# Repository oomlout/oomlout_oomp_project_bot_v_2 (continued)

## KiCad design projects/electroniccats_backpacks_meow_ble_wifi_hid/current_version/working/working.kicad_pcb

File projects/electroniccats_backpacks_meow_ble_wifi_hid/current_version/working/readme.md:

# backpacks_meow
 
## summary 
* id: electroniccats_backpacks_meow_ble_wifi_hid
* user: electroniccats
* name: backpacks_meow
* board: ble_wifi_hid
* repo: https://github.com/ElectronicCats/Backpacks_Meow
* src_file_repo_kicad_pcb: BLE_WIFI_HID/BLE_WIFI_HID.kicad_pcb
* src_file_repo_kicad_pcb_link: https://github.com/ElectronicCats/Backpacks_Meow/tree/master/BLE_WIFI_HID/BLE_WIFI_HID.kicad_pcb

* src_file_repo_sch: BLE_WIFI_HID/BLE_WIFI_HID.sch
* src_file_repo_sch_link: https://github.com/ElectronicCats/Backpacks_Meow/tree/master/BLE_WIFI_HID/BLE_WIFI_HID.sch
* full details link: https://github.com/oomlout/oomlout_oomp_project_bot_v_2/tree/main/projects/electroniccats_backpacks_meow_ble_wifi_hid/current_version/working

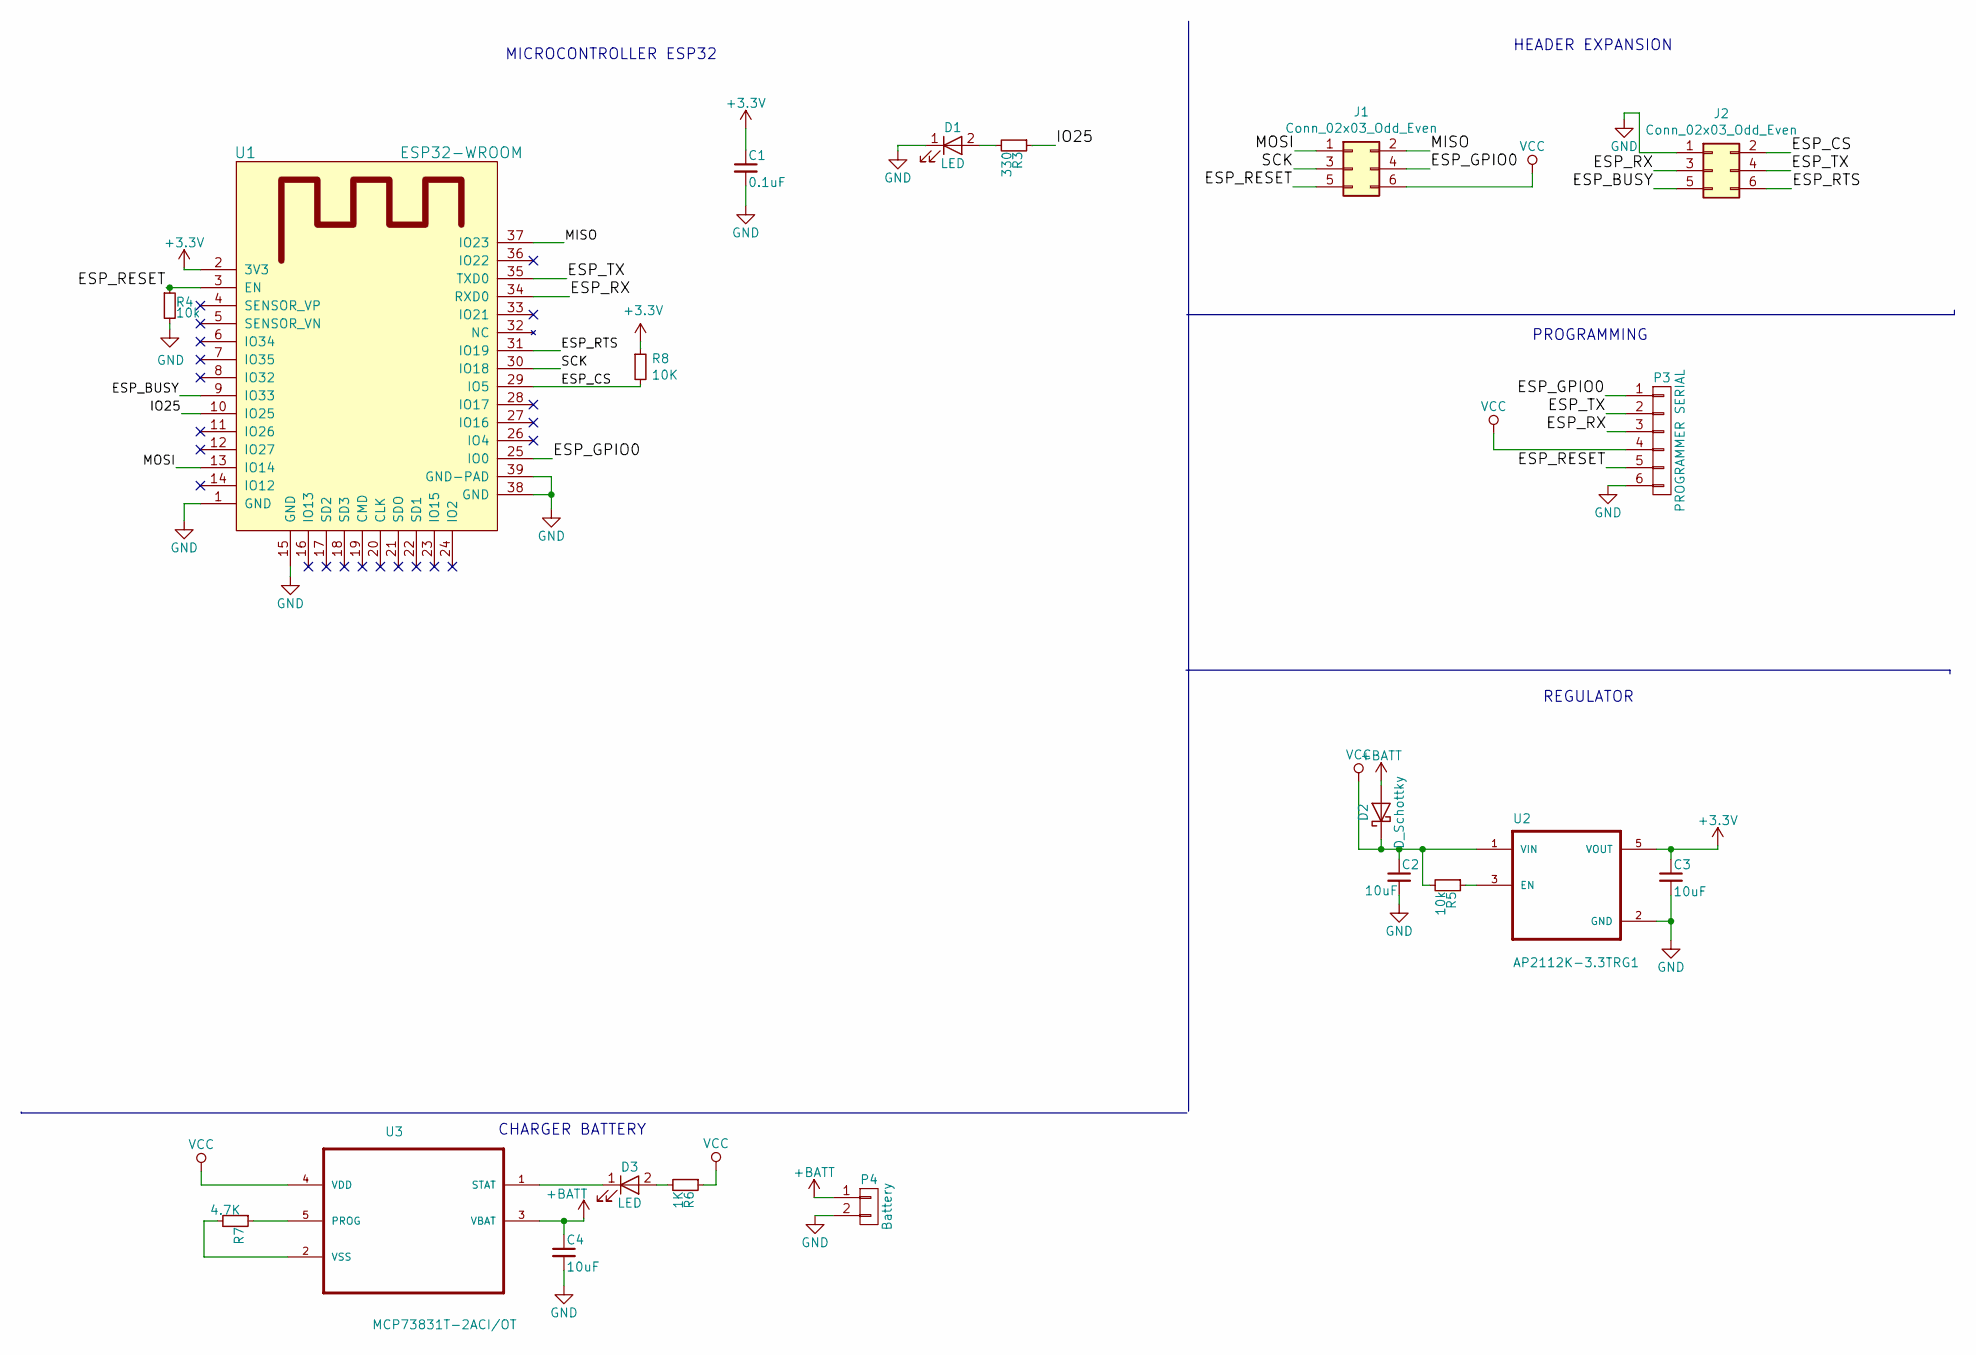
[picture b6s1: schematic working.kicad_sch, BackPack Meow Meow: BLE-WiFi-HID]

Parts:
C1: 0.1uF; C_0805_HandSoldering
C2, C3, C4: 10uF; C_0805_HandSoldering
D1, D3: LED; LED_0805_HandSoldering
D2: D_Schottky; D_SOD-123F
J1, J2: Conn_02x03_Odd_Even; 62000621121
P3: PROGRAMMER SERIAL; Pin_Header_Straight_1x06_Pitch2.54mm
P4: Battery; Pin_Header_Straight_1x02_Pitch2.54mm
R3: 330; R_0805_HandSoldering
R4, R5: 10k; R_0805_HandSoldering
R6: 1K; R_0805_HandSoldering
R7: 4.7K; R_0805_HandSoldering
R8: 10K; R_0805_HandSoldering
U1: ESP32-WROOM
U2: AP2112K-3.3TRG1; SOT-23-5_HandSoldering
U3: MCP73831T-2ACI/OT; SOT-23-5_HandSoldering

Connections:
+3V3: C1.1, C3.1, R8.1, U1.2 (3V3), U2.5 (VOUT)
+BATT: C4.1, D2.2 (A), P4.1, U3.3 (VBAT); also elsewhere on the board
/ESP_BUSY: J2.5, U1.9 (IO33)
/ESP_CS: J2.2, R8.2, U1.29 (IO5)
/ESP_GPIO0: J1.4, P3.1, U1.25 (IO0)
/ESP_RESET: J1.5, P3.5, R4.1, U1.3 (EN)
/ESP_RTS: J2.6, U1.31 (IO19)
/ESP_RX: J2.3, P3.3, U1.34 (RXD0)
/ESP_TX: J2.4, P3.2, U1.35 (TXD0)
/IO25: R3.1, U1.10 (IO25)
/MISO: J1.2, U1.37 (IO23)
/MOSI: J1.1, U1.13 (IO14)
/SCK: J1.3, U1.30 (IO18)
GND: C1.2, C2.2, C3.2, C4.2, D1.1 (K), J2.1, P3.6, P4.2, R4.2, U1.1 (GND), U1.15 (GND), U1.38 (GND), U1.39 (GND-PAD), U2.2 (GND); also elsewhere on the board
unnamed: D1.2 (A), R3.2
unnamed: D3.1 (K), U3.1 (STAT)
unnamed: D3.2 (A), R6.2
unnamed: R5.1, U2.3 (EN)
unnamed: R7.1, U3.5 (PROG)
unnamed: R7.2, U3.2 (VSS)
VCC: C2.1, D2.1 (K), J1.6, P3.4, R5.2, R6.1, U2.1 (VIN), U3.4 (VDD)

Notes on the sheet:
HEADER EXPANSION
MICROCONTROLLER ESP32
CHARGER BATTERY
PROGRAMMING
REGULATOR

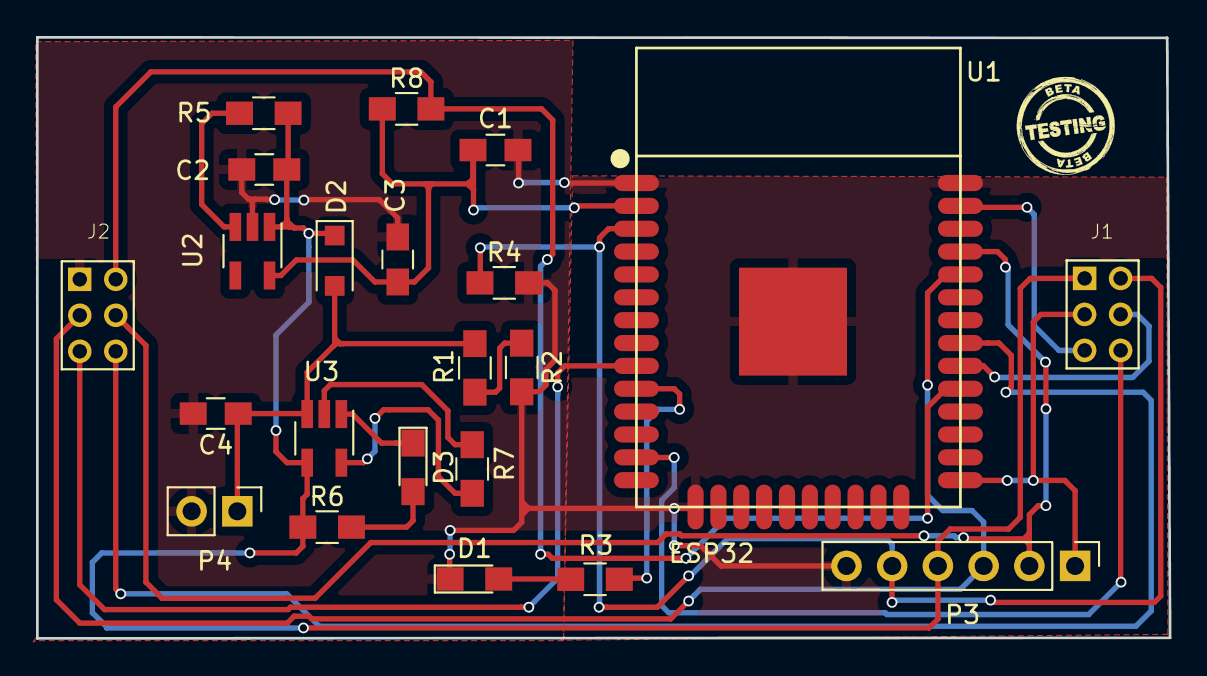
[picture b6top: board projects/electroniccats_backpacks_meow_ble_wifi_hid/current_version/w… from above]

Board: 2 copper layers, 62.9 x 33.4 mm, 22 parts (0 on the bottom side), 22 nets.

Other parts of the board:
R1, R2: 100k; R_0805_HandSoldering

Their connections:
+BATT: R1.1; also elsewhere on the board
/AN35_BAT: R1.2, R2.1
GND: R2.2; also elsewhere on the board

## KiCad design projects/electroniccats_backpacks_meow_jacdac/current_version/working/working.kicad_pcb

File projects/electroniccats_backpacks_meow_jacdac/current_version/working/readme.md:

# backpacks_meow
 
## summary 
* id: electroniccats_backpacks_meow_jacdac
* user: electroniccats
* name: backpacks_meow
* board: jacdac
* repo: https://github.com/ElectronicCats/Backpacks_Meow
* src_file_repo_kicad_pcb: jacdac/jacdac.kicad_pcb
* src_file_repo_kicad_pcb_link: https://github.com/ElectronicCats/Backpacks_Meow/tree/master/jacdac/jacdac.kicad_pcb

* src_file_repo_sch: jacdac/jacdac.sch
* src_file_repo_sch_link: https://github.com/ElectronicCats/Backpacks_Meow/tree/master/jacdac/jacdac.sch
* full details link: https://github.com/oomlout/oomlout_oomp_project_bot_v_2/tree/main/projects/electroniccats_backpacks_meow_jacdac/current_version/working

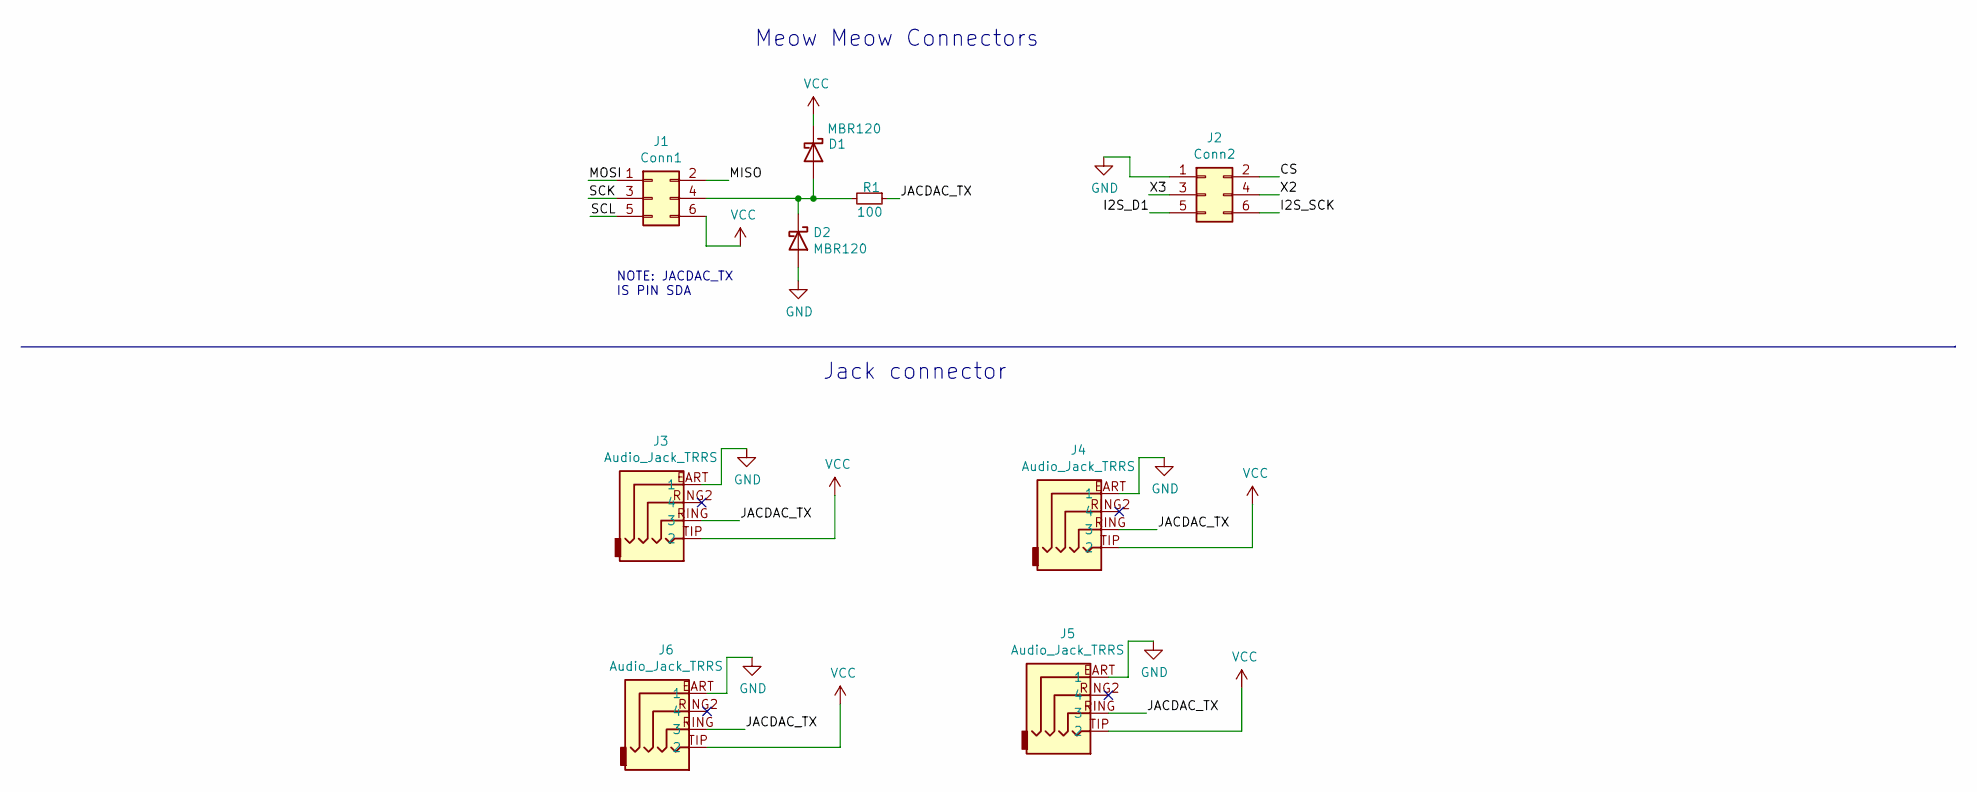
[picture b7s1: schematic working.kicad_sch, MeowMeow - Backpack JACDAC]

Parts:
D1, D2: MBR120; D_SOD-123F
J1: Conn1; 61300621121
J2: Conn2; 61300621121
J3, J4, J5, J6: Audio_Jack_TRRS; AUDIO-JACK-TRRS-SMD
R1: 100; R_0805_HandSoldering

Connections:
/CS: J2.2
/I2S_D1: J2.5
/I2S_SCK: J2.6
/JACDAC_TX: J3.RING (3), J4.RING (3), J5.RING (3), J6.RING (3), R1.1
/MISO: J1.2
/MOSI: J1.1
/SCK: J1.3
/SCL: J1.5
/X2: J2.4
/X3: J2.3
GND: D2.2 (A), J2.1, J3.EART (1), J4.EART (1), J5.EART (1), J6.EART (1)
unnamed: D1.2 (A), D2.1 (K), J1.4, R1.2
VCC: D1.1 (K), J1.6, J3.TIP (2), J4.TIP (2), J5.TIP (2), J6.TIP (2)

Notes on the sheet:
Meow Meow Connectors
NOTE: JACDAC_TX IS PIN SDA
Jack connector

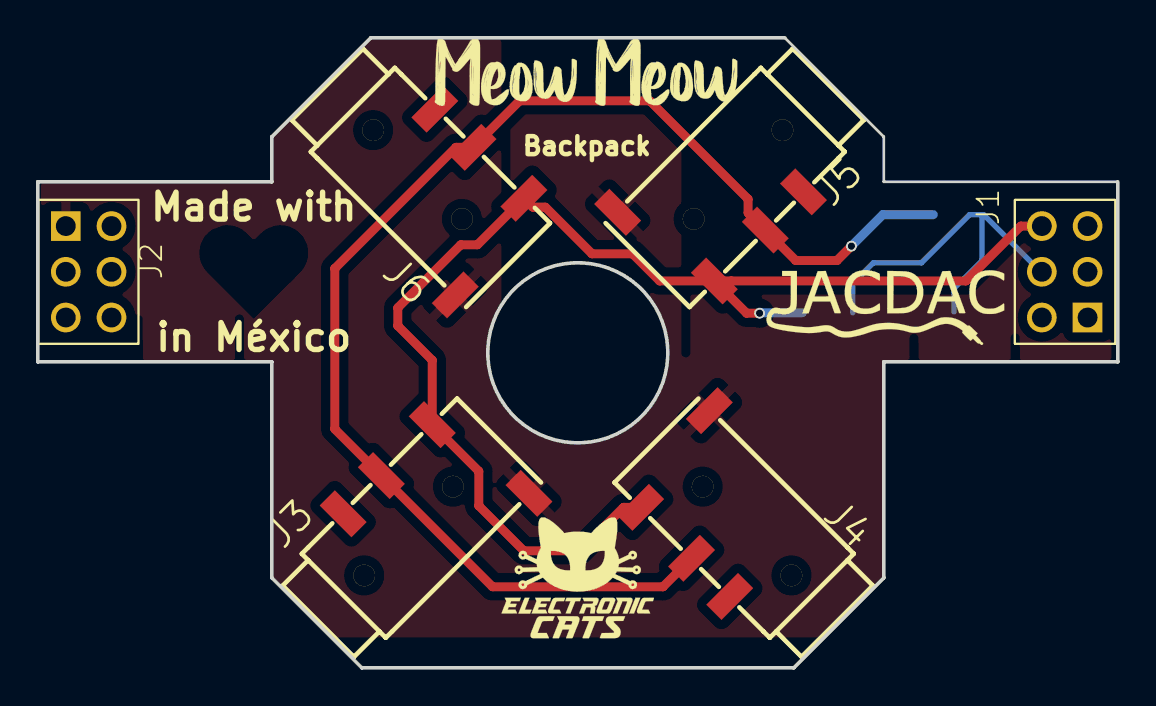
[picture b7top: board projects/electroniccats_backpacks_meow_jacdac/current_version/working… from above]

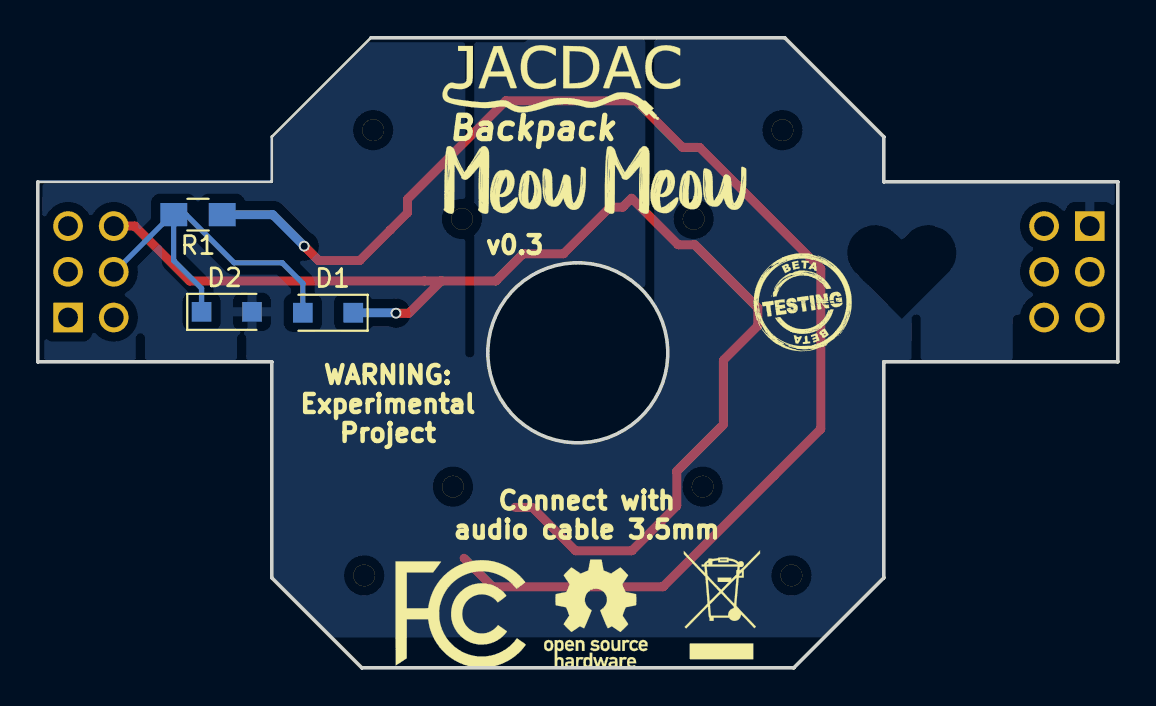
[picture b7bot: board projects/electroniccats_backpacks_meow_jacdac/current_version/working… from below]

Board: 2 copper layers, 60.0 x 35.0 mm, 11 parts (4 on the bottom side), 4 nets.

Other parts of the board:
svg2mod, svg2mod#2: G***; heart_trans

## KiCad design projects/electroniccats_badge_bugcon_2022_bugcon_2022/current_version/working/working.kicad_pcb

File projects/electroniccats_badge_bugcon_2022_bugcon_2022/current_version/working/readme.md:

# badge_bugcon_2022
 
## summary 
* id: electroniccats_badge_bugcon_2022_bugcon_2022
* user: electroniccats
* name: badge_bugcon_2022
* board: bugcon_2022
* repo: https://github.com/ElectronicCats/Badge-BugCON-2022
* src_file_repo_kicad_pcb: Hardware/BugCON-2022.kicad_pcb
* src_file_repo_kicad_pcb_link: https://github.com/ElectronicCats/Badge-BugCON-2022/tree/main/Hardware/BugCON-2022.kicad_pcb
* src_file_repo_kicad_sch: Hardware/BugCON-2022.kicad_sch
* src_file_repo_kicad_sch_link: https://github.com/ElectronicCats/Badge-BugCON-2022/tree/main/Hardware/BugCON-2022.kicad_sch

* src_file_repo_sch: 
* src_file_repo_sch_link: https://github.com/ElectronicCats/Badge-BugCON-2022/tree/main/
* full details link: https://github.com/oomlout/oomlout_oomp_project_bot_v_2/tree/main/projects/electroniccats_badge_bugcon_2022_bugcon_2022/current_version/working

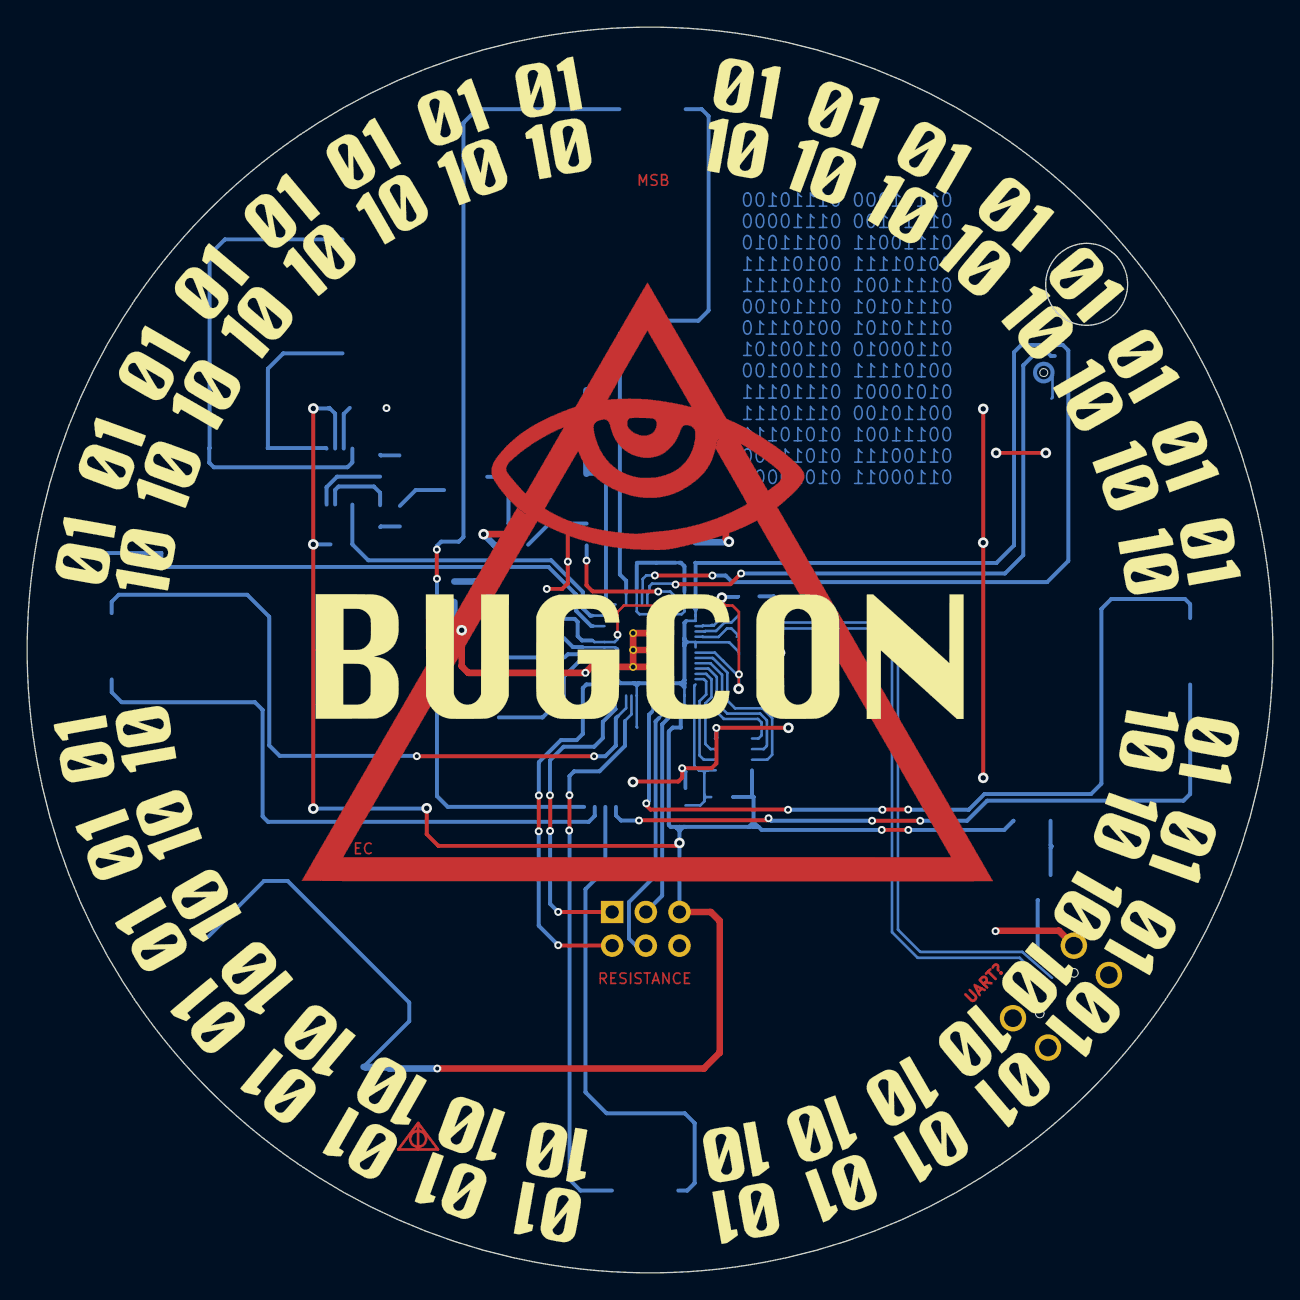
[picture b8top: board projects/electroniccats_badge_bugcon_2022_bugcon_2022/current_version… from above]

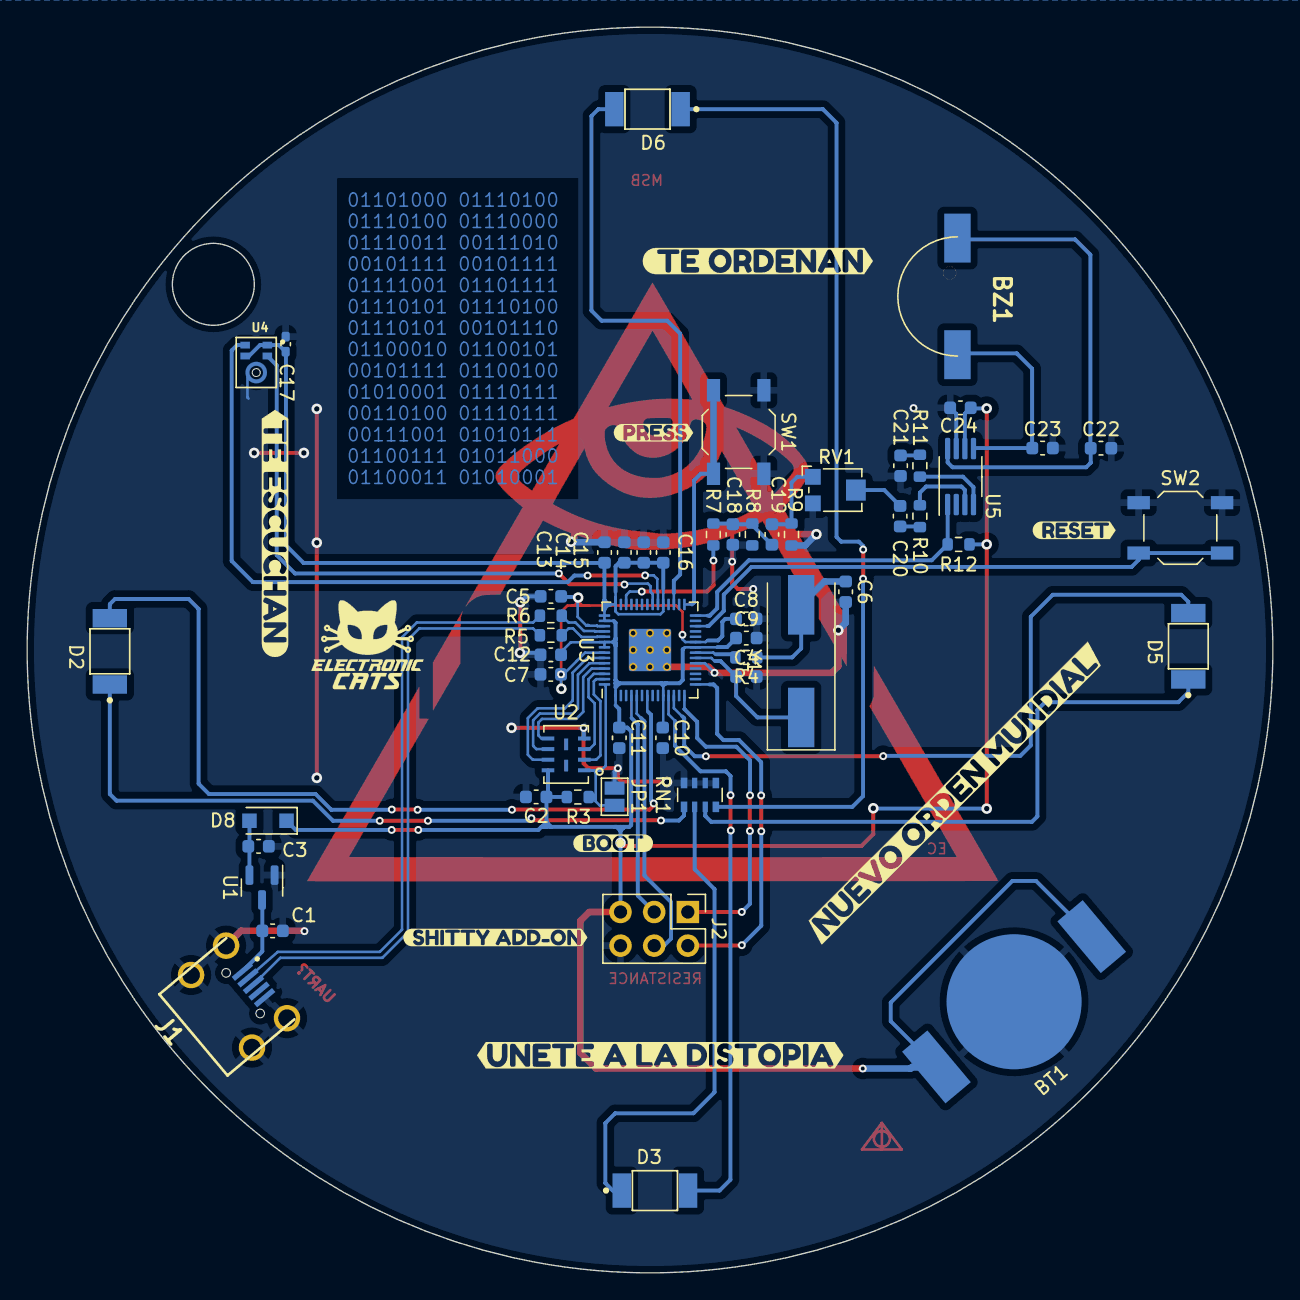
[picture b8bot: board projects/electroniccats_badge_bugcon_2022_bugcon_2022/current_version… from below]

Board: 2 copper layers, 94.0 x 94.0 mm, 63 parts (62 on the bottom side), 45 nets.

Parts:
BT1: Battery_Cell; BAT-HLD-012-SMT-OTL
BZ1: Buzzer; CAPAE1050X250N
C1, C3, C24: 10uF; C_0603_1608Metric
C2, C7, C8, C10, C11, C12, C13, C14, C15, C16: 0.1uF; C_0603_1608Metric
C4, C6: 27pF; C_0603_1608Metric
C5, C9, C20, C21: 1uF; C_0603_1608Metric
C17: 0.1uF; C_0402_1005Metric_Pad0.74x0.62mm_HandSolder
C18: 100nF; C_0603_1608Metric
C19: 47uF; C_0603_1608Metric
C22, C23: 220pF; C_0603_1608Metric
D2, D3, D5, D6: R_LED; LYT77K-K2M1-NoHole
D8: SS1020FL; D_SOD-123F
J1: USB_B_Micro; U254051N4BH806
J2: Conn_02x03_Odd_Even; PinHeader_2x03_P2.54mm_Vertical
JP1: BOOT; SolderJumper-2_P1.3mm_Open_Pad1.0x1.5mm
R3, R12: 10K; R_0603_1608Metric
R4: 1K; R_0603_1608Metric
R5, R6: 27; R_0603_1608Metric
R7: 220; R_0603_1608Metric
R8, R10, R11: 100; R_0603_1608Metric
R9: 1.8K; R_0603_1608Metric
RN1: R_Pack04; R_Array_Convex_4x0603
RV1: 10K; Potentiometer_Bourns_TC33X_Vertical
Ref**: Val**; pin_final_cc
SW1: Button; SW_SPST_TL3342
SW2: RESET; SW_SPST_TL3342
U1: MCP1700-31; SOT-23
U2: W25Q16JV; W25Q16JVUUIQ
U3: RP2040; RP2040-QFN-56
U4: SPH0641LM4H; MIC_SPH0641LM4H-1
U5: PAM8302AAD; MSOP-8_3x3mm_P0.65mm
Y1: 12Mhz; Crystal_SMD_HC49-SD
kibuzzard-6340AD5F: G***; kibuzzard-6340AD5F
kibuzzard-63409D39: G***; kibuzzard-63409D39
kibuzzard-63409DA5: G***; kibuzzard-63409DA5
kibuzzard-63409DC5: G***; kibuzzard-63409DC5
kibuzzard-63409E53: G***; kibuzzard-63409E53
kibuzzard-63409EAE: G***; kibuzzard-63409EAE
kibuzzard-63409EDC: G***; kibuzzard-63409EDC
kibuzzard-63409F0B: G***; kibuzzard-63409F0B

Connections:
+1V2: C5.1, C7.1, C8.1, U3.23 (DVDD), U3.45 (VREG_VOUT), U3.50 (DVDD)
+3V3: BT1.2 (-), C2.1, C9.1, C10.1, C11.1, C12.1, C13.1, C14.1, C15.1, C16.1, C17.1, C24.1, D8.1 (K), J2.5, R3.1, R12.2, U2.8 (VCC), U3.1 (IOVDD), U3.10 (IOVDD), U3.22 (IOVDD), U3.33 (IOVDD), U3.42 (IOVDD), U3.43 (ADC_AVDD), U3.44 (VREG_IN), U3.48 (USB_VDD), U3.49 (IOVDD), U4.1 (VDD), U4.2 (LR), U5.6 (VDD)
/A2: R7.2, U3.40 (GPIO28_ADC2)
/CLK: U3.35 (GPIO23), U4.3 (CLK)
/D0: D2.2 (A), U3.7 (GPIO5)
/D5: D3.2 (A), U3.11 (GPIO8)
/D6: D5.2 (A), U3.12 (GPIO9)
/D10: J2.1, U3.14 (GPIO11)
/D11: J2.2, U3.15 (GPIO12)
/D12: D6.2 (A), U3.31 (GPIO20)
/D+: J1.3 (D+), R5.1
/D-: J1.2 (D-), R6.1
/DOUT: U3.34 (GPIO22), U4.4 (DOUT)
/GPIO17: R12.1, U3.28 (GPIO17), U5.1 (~SD)
/GPIO18: SW1.2, U3.29 (GPIO18)
/QSPI_CS: JP1.2 (B), R3.2, U2.1 (~CS), U3.56 (QSPI_SS)
/QSPI_DATA0: U2.5 (DI(IO0)), U3.53 (QSPI_SD0)
/QSPI_DATA1: U2.2 (DO(IO1)), U3.55 (QSPI_SD1)
/QSPI_DATA2: U2.3 (IO2), U3.54 (QSPI_SD2)
/QSPI_DATA3: U2.7 (IO3), U3.51 (QSPI_SD3)
/QSPI_SCK: U2.6 (CLK), U3.52 (QSPI_SCLK)
/RD+: R5.2, U3.47 (USB_DP)
/RD-: R6.2, U3.46 (USB_DM)
/RST: SW2.2, U3.26 (RUN)
/SCL: J2.4, U3.5 (GPIO3)
/SDA: J2.3, U3.4 (GPIO2)
GND: BT1.1 (+), C1.2, C2.2, C3.2, C4.2, C5.2, C6.2, C7.2, C8.2, C9.2, C10.2, C11.2, C12.2, C13.2, C14.2, C15.2, C16.2, C17.2, C18.2, C21.2, C22.2, C23.2, C24.2, J1.5 (GND), J1.6 (Shield), J2.6, JP1.1 (A), R8.2, R9.2, RN1.5 (R4.2), RN1.6 (R3.2), RN1.7 (R2.2), RN1.8 (R1.2), RV1.3, SW1.1, SW2.1, U1.1 (GND), U2.4 (GND), U3.19 (TESTEN), U3.57 (GND), U4.5 (GND), U5.7 (GND)
unnamed: BZ1.1 (-), C23.1, U5.5 (OUT+)
unnamed: BZ1.2 (+), C22.1, U5.8 (OUT-)
unnamed: C3.1, D8.2 (A), U1.2 (VO)
unnamed: C4.1, U3.20 (XIN), Y1.1
unnamed: C6.1, R4.1, Y1.2
unnamed: C18.1, C19.1, R7.1, R8.1
unnamed: C19.2, R9.1, RV1.1
unnamed: C20.1, RV1.2
unnamed: C20.2, R10.1
unnamed: C21.1, R11.1
unnamed: D2.1 (K), RN1.1 (R1.1)
unnamed: D3.1 (K), RN1.2 (R2.1)
unnamed: D5.1 (K), RN1.3 (R3.1)
unnamed: D6.1 (K), RN1.4 (R4.1)
unnamed: R4.2, U3.21 (XOUT)
unnamed: R10.2, U5.3 (IN+)
unnamed: R11.2, U5.4 (IN-)
VBUS: C1.1, J1.1 (VBUS), U1.3 (VI)
